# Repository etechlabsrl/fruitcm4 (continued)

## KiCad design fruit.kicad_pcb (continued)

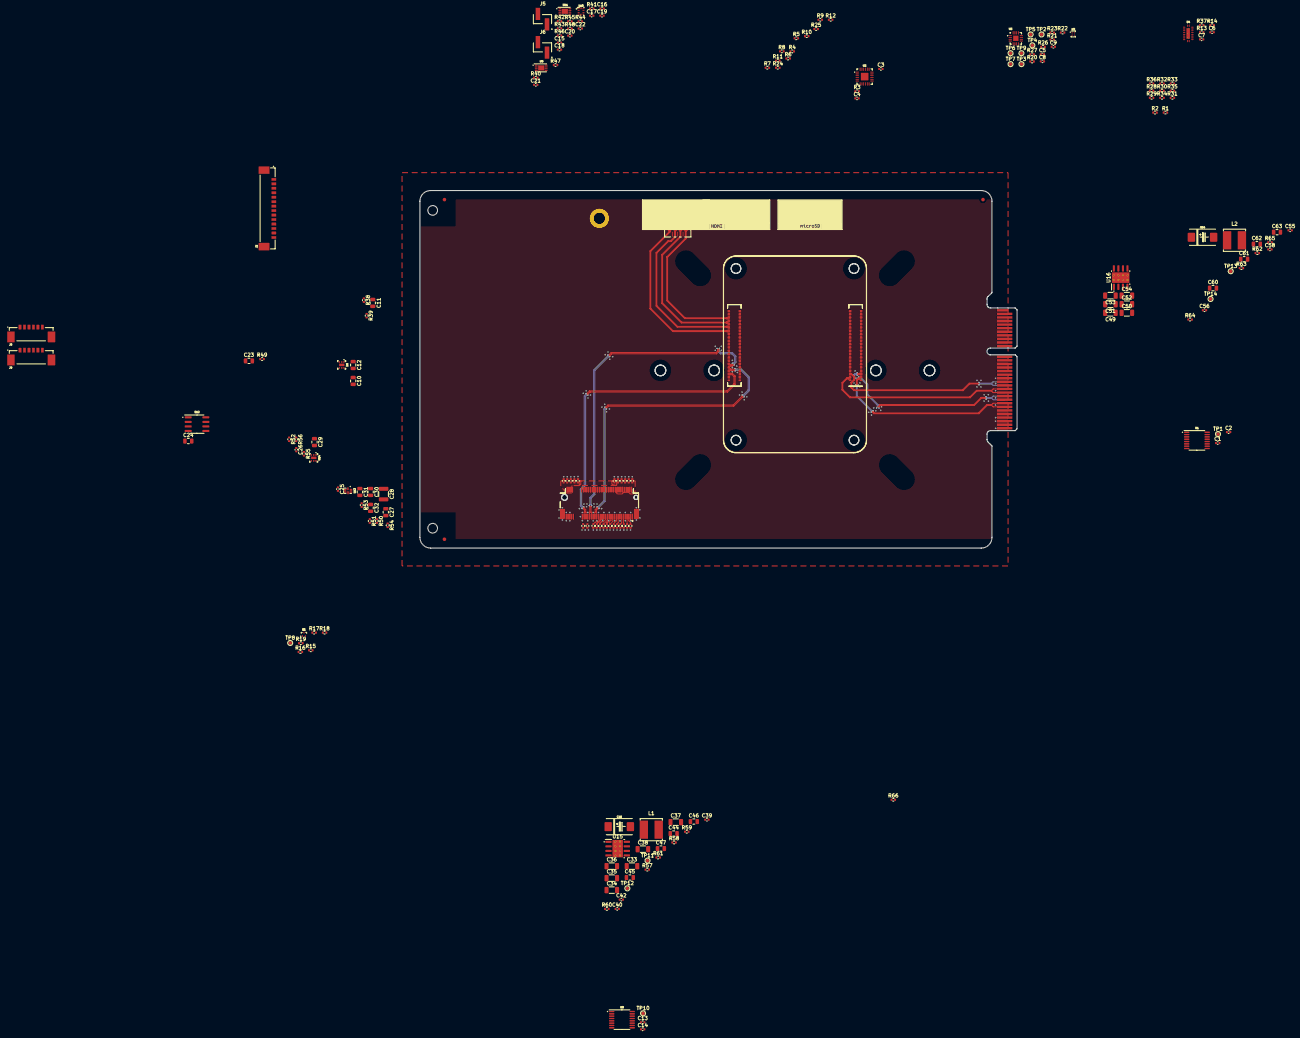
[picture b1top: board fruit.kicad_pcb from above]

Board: 4 copper layers, 167.0 x 100.0 mm, 206 parts (1 on the bottom side), 180 nets.

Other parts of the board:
C1: 10uF; C_0402_1005Metric
C2: 0.1uF; C_0402_1005Metric
CM1#2: ComputeModule4-CM4; Raspberry-Pi-4-Compute-Module_outline
COOLER1#2: 53-61mm_NorthBridge_45deg_arms
J10#2: 1-2199119-6; 1-2199119-6_2280_standoff_nooutline
TP1: TestPoint; TestPoint_Pad_D1.0mm
U1: INA260; TSSOP-16_4.4x5mm_P0.65mm_pin1
kibuzzard-61E49B53: G***; kibuzzard-61E49B53
kibuzzard-61E484E1: G***; kibuzzard-61E484E1

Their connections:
+12V: C1.1, C2.1, U1.5 (A0), U1.10 (VS); also elsewhere on the board
/CM4/CM4 Hirose connectors/GPIO2: CM1#2.58 (GPIO2); also elsewhere on the board
/CM4/CM4 Hirose connectors/GPIO3: CM1#2.56 (GPIO3); also elsewhere on the board
/CM4/CM4 Hirose connectors/GPIO4: CM1#2.54 (GPIO4); also elsewhere on the board
/CM4/CM4 Hirose connectors/GPIO5: CM1#2.34 (GPIO5); also elsewhere on the board
/CM4/CM4 Hirose connectors/GPIO6: CM1#2.30 (GPIO6); also elsewhere on the board
/CM4/CM4 Hirose connectors/GPIO7: CM1#2.37 (GPIO7); also elsewhere on the board
/CM4/CM4 Hirose connectors/GPIO8: CM1#2.39 (GPIO8); also elsewhere on the board
/CM4/CM4 Hirose connectors/GPIO9: CM1#2.40 (GPIO9); also elsewhere on the board
/CM4/CM4 Hirose connectors/GPIO10: CM1#2.44 (GPIO10); also elsewhere on the board
/CM4/CM4 Hirose connectors/GPIO11: CM1#2.38 (GPIO11); also elsewhere on the board
/CM4/CM4 Hirose connectors/GPIO12: CM1#2.31 (GPIO12); also elsewhere on the board
/CM4/CM4 Hirose connectors/GPIO13: CM1#2.28 (GPIO13); also elsewhere on the board
/CM4/CM4 Hirose connectors/GPIO18: CM1#2.49 (GPIO18); also elsewhere on the board
/CM4/CM4 Hirose connectors/GPIO19: CM1#2.26 (GPIO19); also elsewhere on the board
/CM4/CM4 Hirose connectors/GPIO20: CM1#2.27 (GPIO20); also elsewhere on the board
/CM4/CM4 Hirose connectors/GPIO21: CM1#2.25 (GPIO21); also elsewhere on the board
/CM4/CM4 Hirose connectors/GPIO22: CM1#2.46 (GPIO22); also elsewhere on the board
/CM4/CM4 Hirose connectors/ID_SC: CM1#2.35 (ID_SC); also elsewhere on the board
/CM4/CM4 Hirose connectors/ID_SD: CM1#2.36 (ID_SD); also elsewhere on the board
/CM4/CM4 Hirose connectors/~EXTRST: CM1#2.100 (nEXTRST); also elsewhere on the board
/CM4/CM4 PSU/+5V PSU/+5V_OUT: U1.1 (IN+), U1.2 (IN+), U1.3 (IN+), U1.12 (VBUS); also elsewhere on the board
/CM4/CM4_+3.3V: J10#2.2 (3.3V), J10#2.4 (3.3V), J10#2.12 (3.3V), J10#2.14 (3.3V), J10#2.16 (3.3V), J10#2.18 (3.3V), J10#2.70 (3.3V), J10#2.72 (3.3V), J10#2.74 (3.3V); also elsewhere on the board
/CM4/CM4_+5V: CM1#2.77 (+5v_(Input)), CM1#2.79 (+5v_(Input)), CM1#2.81 (+5v_(Input)), CM1#2.83 (+5v_(Input)), CM1#2.85 (+5v_(Input)), CM1#2.87 (+5v_(Input)), TP1.1, U1.14 (IN-), U1.15 (IN-), U1.16 (IN-); also elsewhere on the board
/CM4/CM4_ALERT_+5V: U1.7 (ALERT); also elsewhere on the board
/CM4/CM4_I2C_SCL: CM1#2.80 (SCL0); also elsewhere on the board
/CM4/CM4_I2C_SDA: CM1#2.82 (SDA0); also elsewhere on the board
/CM4/CM4_OUT_+1.8V: CM1#2.88 (+1.8v_(Output)), CM1#2.90 (+1.8v_(Output)); also elsewhere on the board
/CM4/CM4_OUT_+3.3V: CM1#2.78 (GPIO_VREF(1.8v/3.3v_Input)), CM1#2.84 (+3.3v_(Output)), CM1#2.86 (+3.3v_(Output)); also elsewhere on the board
/CM4/HDMICEC: CM1#2.151 (HDMI0_CEC); also elsewhere on the board
/CM4/HDMICK+: CM1#2.188 (HDMI0_CLK_P); also elsewhere on the board
/CM4/HDMICK-: CM1#2.190 (HDMI0_CLK_N); also elsewhere on the board
/CM4/HDMID0+: CM1#2.182 (HDMI0_TX0_P); also elsewhere on the board
/CM4/HDMID0-: CM1#2.184 (HDMI0_TX0_N); also elsewhere on the board
/CM4/HDMID1+: CM1#2.176 (HDMI0_TX1_P); also elsewhere on the board
/CM4/HDMID1-: CM1#2.178 (HDMI0_TX1_N); also elsewhere on the board
/CM4/HDMID2+: CM1#2.170 (HDMI0_TX2_P); also elsewhere on the board
/CM4/HDMID2-: CM1#2.172 (HDMI0_TX2_N); also elsewhere on the board
/CM4/HDMIHP: CM1#2.153 (HDMI0_HOTPLUG); also elsewhere on the board
/CM4/HDMISCL: CM1#2.200 (HDMI0_SCL); also elsewhere on the board
/CM4/HDMISDA: CM1#2.199 (HDMI0_SDA); also elsewhere on the board
/CM4/I2C_GLOBAL_EN: CM1#2.99 (Global_EN); also elsewhere on the board
/CM4/I2C_RUN_PG: CM1#2.92 (RUN_PG); also elsewhere on the board
/CM4/I2C_SCL: U1.9 (SCL); also elsewhere on the board
/CM4/I2C_SDA: U1.8 (SDA); also elsewhere on the board
/CM4/M2_1_ACTIVITY_LED: J10#2.10 (DAS/DSS); also elsewhere on the board
/CM4/PCIE_CLK+: CM1#2.110 (PCIe_CLK_P), J10#2.55 (REFCLK+); also elsewhere on the board
/CM4/PCIE_CLK-: CM1#2.112 (PCIe_CLK_N), J10#2.53 (REFCLK-); also elsewhere on the board
/CM4/PCIE_RX+: CM1#2.116 (PCIe_RX_P), J10#2.43 (PER0+); also elsewhere on the board
/CM4/PCIE_RX-: CM1#2.118 (PCIe_RX_N), J10#2.41 (PER0-); also elsewhere on the board
/CM4/PCIE_TX+: CM1#2.122 (PCIe_TX_P), J10#2.47 (PET0-); also elsewhere on the board
/CM4/PCIE_TX-: CM1#2.124 (PCIe_TX_N), J10#2.49 (PET0+); also elsewhere on the board
/CM4/SD_CLK: CM1#2.57 (SD_CLK); also elsewhere on the board
/CM4/SD_CMD: CM1#2.62 (SD_CMD); also elsewhere on the board
/CM4/SD_DAT0: CM1#2.63 (SD_DAT0); also elsewhere on the board
/CM4/SD_DAT1: CM1#2.67 (SD_DAT1); also elsewhere on the board
/CM4/SD_DAT2: CM1#2.69 (SD_DAT2); also elsewhere on the board
/CM4/SD_DAT3: CM1#2.61 (SD_DAT3); also elsewhere on the board
/CM4/SD_PWR_ON: CM1#2.75 (SD_PWR_ON); also elsewhere on the board
/CM4/SOFT_HALT: CM1#2.24 (GPIO26); also elsewhere on the board
/CM4/SOFT_REBOOT: CM1#2.48 (GPIO27); also elsewhere on the board
/CM4/USB+: CM1#2.105 (USB2_P); also elsewhere on the board
/CM4/USB-: CM1#2.103 (USB2_N); also elsewhere on the board
/CM4/USBOTG: CM1#2.101 (USB_OTG_ID); also elsewhere on the board
/CM4/~EthLED1: CM1#2.19 (Ethernet_nLED1(3.3v)); also elsewhere on the board
/CM4/~EthLED2: CM1#2.17 (Ethernet_nLED2(3.3v)); also elsewhere on the board
/CM4/~EthLED3: CM1#2.15 (Ethernet_nLED3(3.3v)); also elsewhere on the board
/CM4/~I2C_RPI_BOOT: CM1#2.93 (nRPIBOOT); also elsewhere on the board
/CM4/~INT_CM4: CM1#2.47 (GPIO23); also elsewhere on the board
/CM4/~PANIC_CM4: CM1#2.45 (GPIO24); also elsewhere on the board
/CM4/~PCIE_CLK_REQ: CM1#2.102 (PCIe_CLK_nREQ), J10#2.52 (~CLKREQ); also elsewhere on the board
/CM4/~PCIE_RST: CM1#2.109 (PCIe_nRST), J10#2.50 (~PERST); also elsewhere on the board
/CM4/~PI_Activity: CM1#2.21 (PI_nLED_Activity); also elsewhere on the board
/CM4/~PWR_LED: CM1#2.95 (nPI_LED_PWR); also elsewhere on the board
/EthA+: CM1#2.12 (Ethernet_Pair0_P); also elsewhere on the board
/EthA-: CM1#2.10 (Ethernet_Pair0_N); also elsewhere on the board
/EthB+: CM1#2.4 (Ethernet_Pair1_P); also elsewhere on the board
/EthB-: CM1#2.6 (Ethernet_Pair1_N); also elsewhere on the board
/EthC+: CM1#2.11 (Ethernet_Pair2_P); also elsewhere on the board
/EthC-: CM1#2.9 (Ethernet_Pair2_N); also elsewhere on the board
/EthD+: CM1#2.3 (Ethernet_Pair3_P); also elsewhere on the board
/EthD-: CM1#2.5 (Ethernet_Pair3_N); also elsewhere on the board
/UART_CTS1: CM1#2.29 (GPIO16); also elsewhere on the board
/UART_RTS1: CM1#2.50 (GPIO17); also elsewhere on the board
/UART_RXD1: CM1#2.51 (GPIO15); also elsewhere on the board
/UART_TXD1: CM1#2.55 (GPIO14); also elsewhere on the board
/~I2C_RESET: CM1#2.41 (GPIO25); also elsewhere on the board
GND: C1.2, C2.2, CM1#2.1 (GND), CM1#2.2 (GND), CM1#2.7 (GND), CM1#2.8 (GND), CM1#2.13 (GND), CM1#2.14 (GND), CM1#2.22 (GND), CM1#2.23 (GND), CM1#2.32 (GND), CM1#2.33 (GND), CM1#2.42 (GND), CM1#2.43 (GND), CM1#2.52 (GND), CM1#2.53 (GND), CM1#2.59 (GND), CM1#2.60 (GND), CM1#2.65 (GND), CM1#2.66 (GND), CM1#2.71 (GND), CM1#2.74 (GND), CM1#2.89 (WiFi_nDisable), CM1#2.91 (BT_nDisable), CM1#2.98 (GND), CM1#2.107 (GND), CM1#2.108 (GND), CM1#2.113 (GND), CM1#2.114 (GND), CM1#2.119 (GND), CM1#2.120 (GND), CM1#2.125 (GND), CM1#2.126 (GND), CM1#2.131 (GND), CM1#2.132 (GND), CM1#2.137 (GND), CM1#2.138 (GND), CM1#2.144 (GND), CM1#2.150 (GND), CM1#2.155 (GND), CM1#2.156 (GND), CM1#2.161 (GND), CM1#2.162 (GND), CM1#2.167 (GND), CM1#2.168 (GND), CM1#2.173 (GND), CM1#2.174 (GND), CM1#2.179 (GND), CM1#2.180 (GND), CM1#2.185 (GND), CM1#2.186 (GND), CM1#2.191 (GND), CM1#2.192 (GND), CM1#2.197 (GND), CM1#2.198 (GND), J10#2.1 (GND), J10#2.3 (GND), J10#2.9 (GND), J10#2.15 (GND), J10#2.21 (GND), J10#2.27 (GND), J10#2.33 (GND), J10#2.39 (GND), J10#2.45 (GND), J10#2.51 (GND), J10#2.57 (GND), J10#2.71 (GND), J10#2.73 (GND), J10#2.75 (GND), J10#2.S (SHIELD), U1.4 (A1), U1.6 (GND), U1.11 (GND); also elsewhere on the board
unnamed 152: J10#2.5 (PER3-); also elsewhere on the board
unnamed 153: J10#2.7 (PER+); also elsewhere on the board
unnamed 154: J10#2.11 (PET3-); also elsewhere on the board
unnamed 155: J10#2.13 (PET3+); also elsewhere on the board
unnamed 156: J10#2.17 (PER2-); also elsewhere on the board
unnamed 157: J10#2.19 (PER2+); also elsewhere on the board
unnamed 158: J10#2.23 (PET2-); also elsewhere on the board
unnamed 159: J10#2.25 (PET2+); also elsewhere on the board
unnamed 160: J10#2.29 (PER1-); also elsewhere on the board
unnamed 161: J10#2.31 (PER1+); also elsewhere on the board
unnamed 162: J10#2.35 (PET1-); also elsewhere on the board
unnamed 163: J10#2.37 (PET1+); also elsewhere on the board

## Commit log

2022-01-11 init
2022-01-11 respin
2022-01-11 cosmetic
2022-01-11 moved m.2 socket around
2022-01-12 locked cm4 & mech footprints
2022-01-12 fixed I2C ping indicator
2022-01-12 added inverter lib
2022-01-12 swapped transistor libs
2022-01-12 added ti buffer lib
2022-01-12 more indicator fixes
2022-01-12 initial integration of i2c arbiter
2022-01-12 refresh
2022-01-12 footprint assignment
2022-01-12 symbol bug fix
2022-01-12 board refresh
2022-01-13 schematic cleanup
2022-01-14 work on control logic
2022-01-15 schematic sheet renames
2022-01-15 schematic bug fixes
2022-01-15 layout experiments
2022-01-15 dp routing
2022-01-16 merging changes for face plate conn
2022-01-16 refresh artifacts
2022-01-16 connecterized faceplate, refreshed schematic
2022-01-16 placed hdmi conn
2022-01-16 hdmi dp routing
2022-01-16 hdmi dp routed
2022-01-16 microsd conn placed
2022-01-17 hdmi dp cleanup
2022-01-17 gnd vias
2022-01-17 leds
2022-01-17 led changes
2022-01-21 trued up facecm4 connector pinout
